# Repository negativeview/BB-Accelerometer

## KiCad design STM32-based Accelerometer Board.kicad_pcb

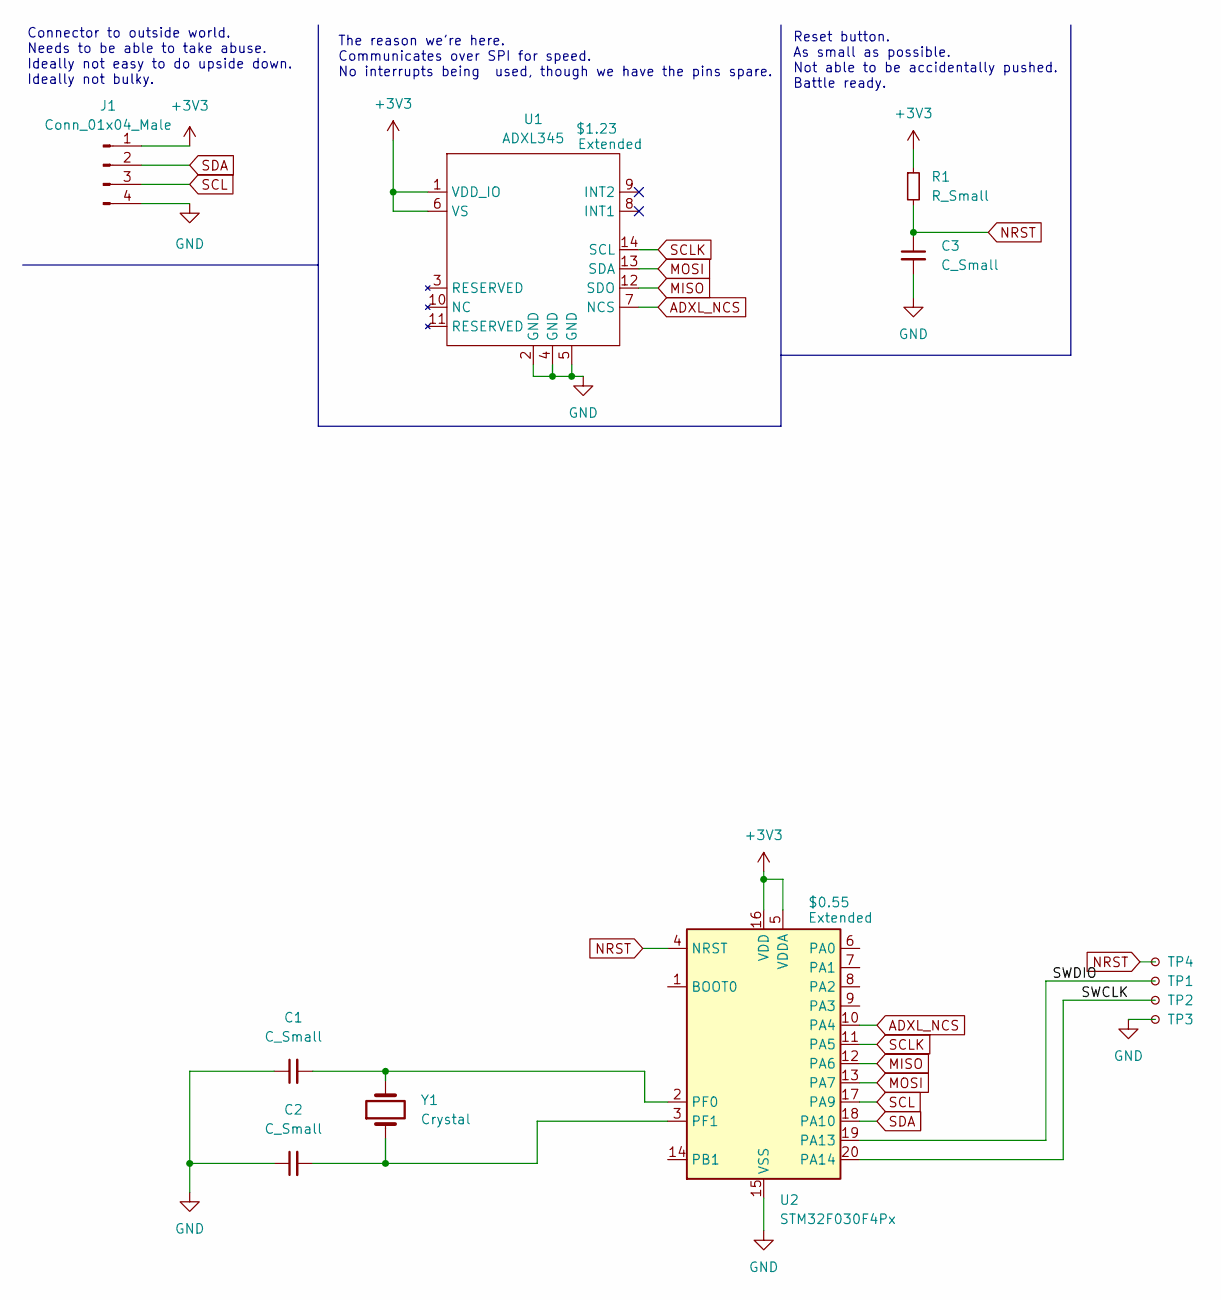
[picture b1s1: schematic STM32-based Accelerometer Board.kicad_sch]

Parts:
C1, C2, C3: C_Small; C_0603_1608Metric_Pad1.08x0.95mm_HandSolder
J1: Conn_01x04_Male; JST_GH_BM04B-GHS-TBT_1x04-1MP_P1.25mm_Vertical
R1: R_Small; R_0603_1608Metric_Pad0.98x0.95mm_HandSolder
TP1, TP2, TP3, TP4: TestPoint_Small; TestPoint_Pad_1.0x1.0mm
U1: ADXL345; LGA-14_3x5mm_P0.8mm_LayoutBorder1x6y; JLCPCB Status Extended
U2: STM32F030F4Px; TSSOP-20_4.4x6.5mm_P0.65mm; JLCPCB Status Extended
Y1: Crystal; Crystal_SMD_0603-2Pin_6.0x3.5mm_HandSoldering

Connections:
+3V3: J1.1, R1.1, U1.1 (VDD_IO), U1.6 (VS), U2.5 (VDDA), U2.16 (VDD)
/SWCLK: TP2.1, U2.20 (PA14)
/SWDIO: TP1.1, U2.19 (PA13)
ADXL_NCS: U1.7 (NCS), U2.10 (PA4)
GND: C1.1, C2.1, C3.2, J1.4, TP3.1, U1.2 (GND), U1.4 (GND), U1.5 (GND), U2.15 (VSS)
MISO: U1.12 (SDO), U2.12 (PA6)
MOSI: U1.13 (SDA), U2.13 (PA7)
NRST: C3.1, R1.2, TP4.1, U2.4 (NRST)
unnamed: C1.2, U2.2 (PF0), Y1.2
unnamed: C2.2, U2.3 (PF1), Y1.1
SCL: J1.3, U2.17 (PA9)
SCLK: U1.14 (SCL), U2.11 (PA5)
SDA: J1.2, U2.18 (PA10)

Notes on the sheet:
Reset button. As small as possible. Not able to be accidentally pushed. Battle ready.
Connector to outside world. Needs to be able to take abuse. Ideally not easy to do upside down. Ideally not bulky.
The reason we're here. Communicates over SPI for speed. No interrupts being used, though we have the pins spare.

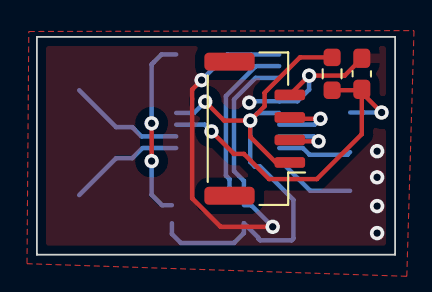
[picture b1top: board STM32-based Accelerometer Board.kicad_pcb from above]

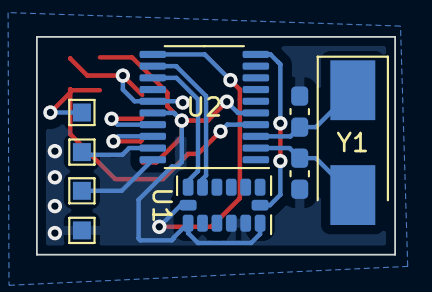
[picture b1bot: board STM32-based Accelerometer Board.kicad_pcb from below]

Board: 2 copper layers, 19.9 x 12.1 mm, 12 parts (9 on the bottom side), 13 nets.

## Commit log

2023-10-31 Initial commit.
2023-11-01 Smaller! Think there's low-hanging fruit, but saving status.
